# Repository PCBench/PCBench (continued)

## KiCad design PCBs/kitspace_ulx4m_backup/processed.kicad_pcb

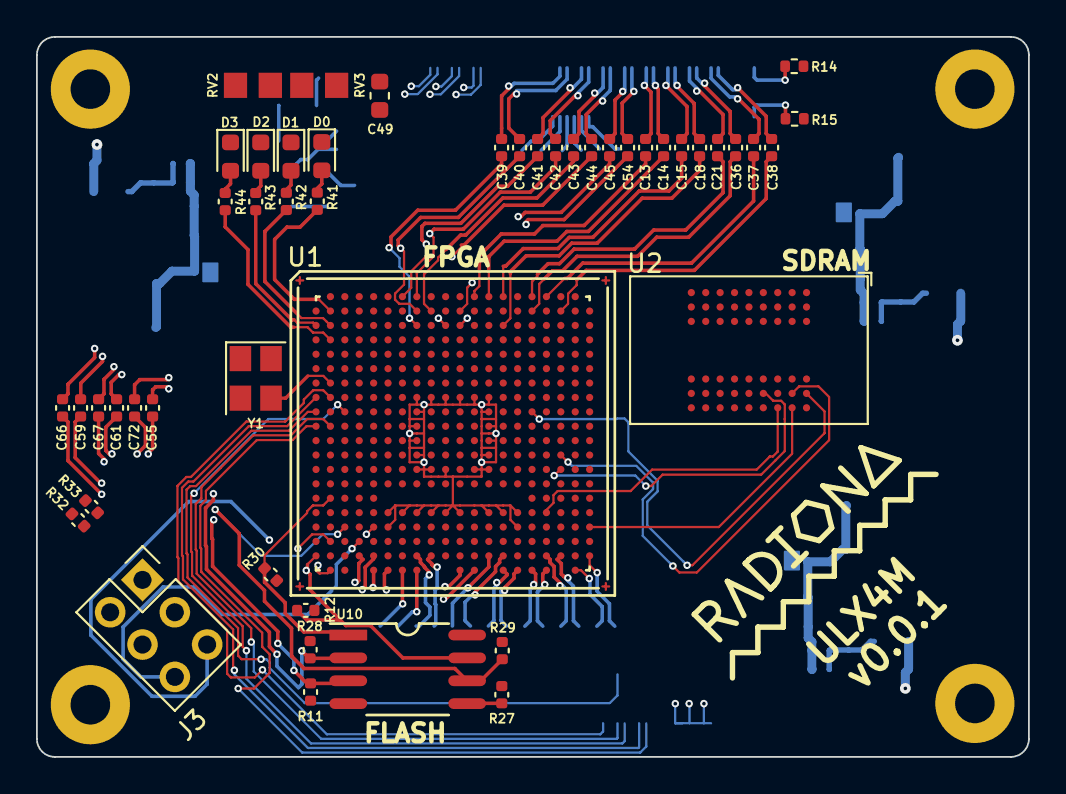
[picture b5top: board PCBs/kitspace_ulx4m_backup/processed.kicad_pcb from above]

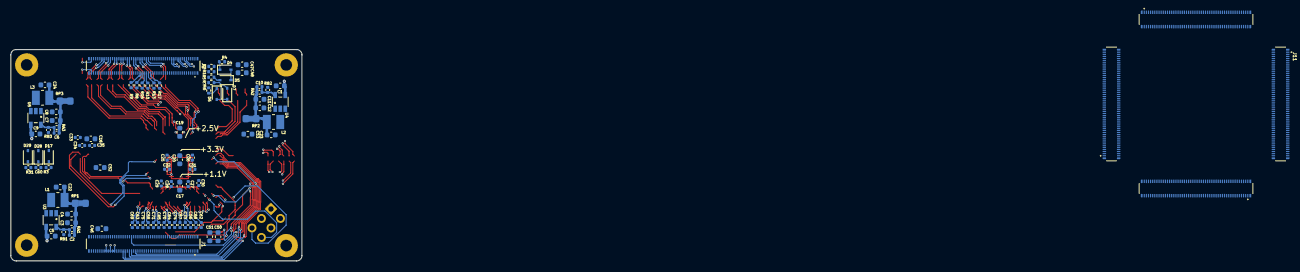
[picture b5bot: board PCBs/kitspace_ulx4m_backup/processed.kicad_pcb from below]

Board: 4 copper layers, 55.1 x 40.0 mm, 151 parts (96 on the bottom side), 108 nets.

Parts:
C1, C3, C4, C5, C7, C8, C9, C11, C12: 22uF; C_0603_1608Metric
C2, C6, C10: 100pF; C_0402_1005Metric
C13, C14, C15, C18, C21, C36, C37, C38, C39, C40, C41, C42, C43, C44, C45, C54: 100n; C_0402_1005Metric
C16, C17, C19, C20, C22, C23, C24, C46, C47: 2.2uF; C_0603_1608Metric
C25, C26, C27, C28, C29, C30, C31, C32, C33, C34, C35: 22nF; C_0402_1005Metric
C48, C49, C50, C51, C52, C53: 22nF; C_0603_1608Metric
C55, C56, C57, C58, C59, C61, C62, C63, C64, C65, C66, C67, C68, C69, C70, C71, C72, C73, C74, C75: 22n; C_0402_1005Metric
C60: 220nF; C_0402_1005Metric
D0: RED; LED_0603_1608Metric
D1: ORANGE; LED_0603_1608Metric
D2: GREEN; LED_0603_1608Metric
D3: BLUE; LED_0603_1608Metric
D4, D5, D6, D7, D17, D28, D29: 1N914; D_SOD-323
EMARD: emard12mm
EMARD#2: emard12mm
H1, H2, H3, H4: HOLE; MountingHole_3.2mm_M3_ISO14580_Pad
J1, J2, J9, J10, J11, J12: DF40C-100DP-0.4V(51); HRS_DF40C-100DP-0.4V(51)
J3: JTAG; PinSocket_2x03_P2.54mm_Vertical
L1, L2, L3: 2.2uH; L_1008_1210
R1, R2: 27; R_0402_1005Metric
R3, R30: 4.7k; C_0402_1005Metric
R4, R6: 1.1K; R_0402_1005Metric
R5, R7: 15K; R_0402_1005Metric
R8, R9, R16, R17: 100K; R_0402_1005Metric
R10, R13, R14, R15: 4K7; R_0402_1005Metric
R11, R12, R27, R28: 10k; C_0402_1005Metric
R29: 1.1k; C_0402_1005Metric
R31, R32, R33: 15k; C_0402_1005Metric
R41, R42, R43, R44: 549; C_0402_1005Metric
RA1, RA2, RA3: 15k; C_0402_1005Metric
RB1: 18k; C_0402_1005Metric
RB2: 4.7k; C_0402_1005Metric
RB3: 3.3k; C_0402_1005Metric
RP1, RP2, RP3: 0; R_0805_2012Metric_Pad1.29x1.40mm_HandSolder_Jumper_NC
RV2, RV3: 0; R_0805_2012Metric_Pad1.29x1.40mm_HandSolder
U1: LFE5U-85F-6BG381C; BGA-381_pitch0.8mm_dia0.4mm
U2: IS42S16320D-6BLI
U3, U4, U5: TLV62569DBV; TSOT-25
U10: IS25LP128F-JBLE; SOA008-150-208mil
Y1: FNETHE025; Crystal_SMD_TXC_7M-4Pin_3.2x2.5mm
fer: fer; fer4mm6
koncar: koncar
radiona: radiona

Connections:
+1V1: U1.H8, U1.H9, U1.H10, U1.H11, U1.H12, U1.H13, U1.J8, U1.J13, U1.K8, U1.K13, U1.L8, U1.L13, U1.M8, U1.M13, U1.N8, U1.N9, U1.N10, U1.N12, U1.N13, U1.T6, U1.T7, U1.T8, U1.T9, U1.T10, U1.T11, U1.T13, U1.T14, U1.T15, U1.U6, U1.U15
+5V: C1.1, C5.1, C9.1, J1.77, J1.79, J1.81, J1.85, J1.87, U3.4, U4.4, U5.4
/blinkey/ALED0: D0.2, R41.2
/blinkey/ALED1: D1.2, R42.2
/blinkey/ALED2: D2.2, R43.2
/blinkey/ALED3: D3.2, R44.2
/flash/FLASH_MISO: R28.2, U1.V2, U10.2
/flash/FLASH_MOSI: R27.2, U10.5
/flash/FLASH_SCK: R29.2, U1.U3, U10.6
/flash/FLASH_nCS: R30.2, U1.R2, U10.1
/flash/FLASH_nHOLD: R12.2, U1.W1, U10.7
/flash/FLASH_nWP: R11.2, U1.Y2, U10.3
/power/FB1: C2.2, RA1.2, RB1.2, U3.5
/power/FB2: C10.2, RA2.2, RB2.2, U4.5
/power/FB3: C6.2, RA3.2, RB3.2, U5.5
/power/P1V1: C2.1, C3.1, C4.1, C22.1, L1.2, RA1.1
/power/P2V5: C10.1, C11.1, C12.1, C23.1, L2.2, RA2.1
/power/P3V3: C6.1, C7.1, C8.1, C24.1, L3.2, RA3.1
/serdes/CLK_0_N: C66.1, U1.Y12
/serdes/CLK_0_P: C59.2, U1.Y11
/serdes/CLK_1_N: C69.1, U1.W20
/serdes/CLK_1_P: C63.2, U1.Y19
/serdes/S_0_N: C67.1, U1.Y6
/serdes/S_0_P: C61.2, U1.Y5
/serdes/S_1_N: C68.1, U1.Y8
/serdes/S_1_P: C62.2, U1.Y7
/serdes/S_2_N: C72.1, U1.W5
/serdes/S_2_P: C55.2, U1.W4
/serdes/S_3_N: C73.1, U1.W9
/serdes/S_3_P: C56.2, U1.W8
/serdes/S_4_N: C70.1, U1.Y15
/serdes/S_4_P: C64.2, U1.Y14
/serdes/S_5_N: C71.1, U1.Y17
/serdes/S_5_P: C65.2, U1.Y16
/serdes/S_6_N: C74.1, U1.W14
/serdes/S_6_P: C57.2, U1.W13
/serdes/S_7_N: C75.1, U1.W18
/serdes/S_7_P: C58.2, U1.W17
CLK_25MHz: U1.G2, Y1.3
FPDI_CLK+: C37.1, U1.A17
FPDI_CLK-: C38.1, U1.B18
FPDI_D0+: C21.1, U1.A16
FPDI_D0-: C36.1, U1.B16
FPDI_D1+: C15.1, U1.A14
FPDI_D1-: C18.1, U1.C14
FPDI_D2+: C13.1, U1.A12
FPDI_D2-: C14.1, U1.A13
GN0: C54.1, U1.C11
GN3: C44.1, U1.C10
GN4: C42.1, U1.A8
GN5: C40.1, U1.B8
GP0: C45.1, U1.B11
GP3: C43.1, U1.B9
GP4: C41.1, U1.A7
GP5: C39.1, U1.C8
HDMI0_CEC: J2.51, R8.2
HDMI0_CLK_N: C38.2, J2.90
HDMI0_CLK_P: C37.2, J2.88
HDMI0_HOTPLUG: J2.53, R9.2
HDMI0_SCL: J2.100, R14.2
HDMI0_SDA: J2.99, R15.2
HDMI0_TX0_N: C36.2, J2.84
HDMI0_TX0_P: C21.2, J2.82
HDMI0_TX1_N: C18.2, J2.78
HDMI0_TX1_P: C15.2, J2.76
HDMI0_TX2_N: C14.2, J2.72
HDMI0_TX2_P: C13.2, J2.70
HDMI1_CEC: J2.49, R16.2
HDMI1_CLK_N: C54.2, J2.66
HDMI1_CLK_P: C45.2, J2.64
HDMI1_HOTPLUG: J2.43, R17.2
HDMI1_SCL: J2.47, R10.2
HDMI1_SDA: J2.45, R13.2
HDMI1_TX0_N: C44.2, J2.60
HDMI1_TX0_P: C43.2, J2.58
HDMI1_TX1_N: C42.2, J2.54
HDMI1_TX1_P: C41.2, J2.52
HDMI1_TX2_N: C40.2, J2.48
HDMI1_TX2_P: C39.2, J2.46
JTAG_TDO: J3.6, U1.V4
JTAG_TMS: J3.5, U1.U5
LED0: R41.1, U1.B2
LED1: R42.1, U1.C2
LED2: R43.1, U1.C1
LED3: R44.1, U1.D2
unnamed: D4.1, R4.1
unnamed: D5.2, R5.1
unnamed: D6.1, R6.1
unnamed: D7.2, R7.1
PCIe_CLK_N: C66.2, J2.12
PCIe_CLK_P: C59.1, J2.10
PCIe_RX_N: C67.2, J2.18
PCIe_RX_P: C61.1, J2.16
PCIe_TX_N: C72.2, J2.24
PCIe_TX_P: C55.1, J2.22
SDRAM_D0: U1.J16, U2.A8
SDRAM_D2: U1.M18, U2.B8
SDRAM_D3: U1.N18, U2.D8
SDRAM_D6: U1.T17, U2.C9
SDRAM_D7: U1.U20, U2.B9
SD_CLK: J1.57, U1.H2
SD_CMD: J1.62, U1.J1
SD_D0: J1.63, U1.J3
SD_D1: J1.67, U1.H1
SD_D2: J1.69, U1.K1
SD_D3: J1.61, U1.K2
USB_FPGA_PULL_D+: D4.2, D5.1
USB_FPGA_PULL_D-: D6.2, D7.1

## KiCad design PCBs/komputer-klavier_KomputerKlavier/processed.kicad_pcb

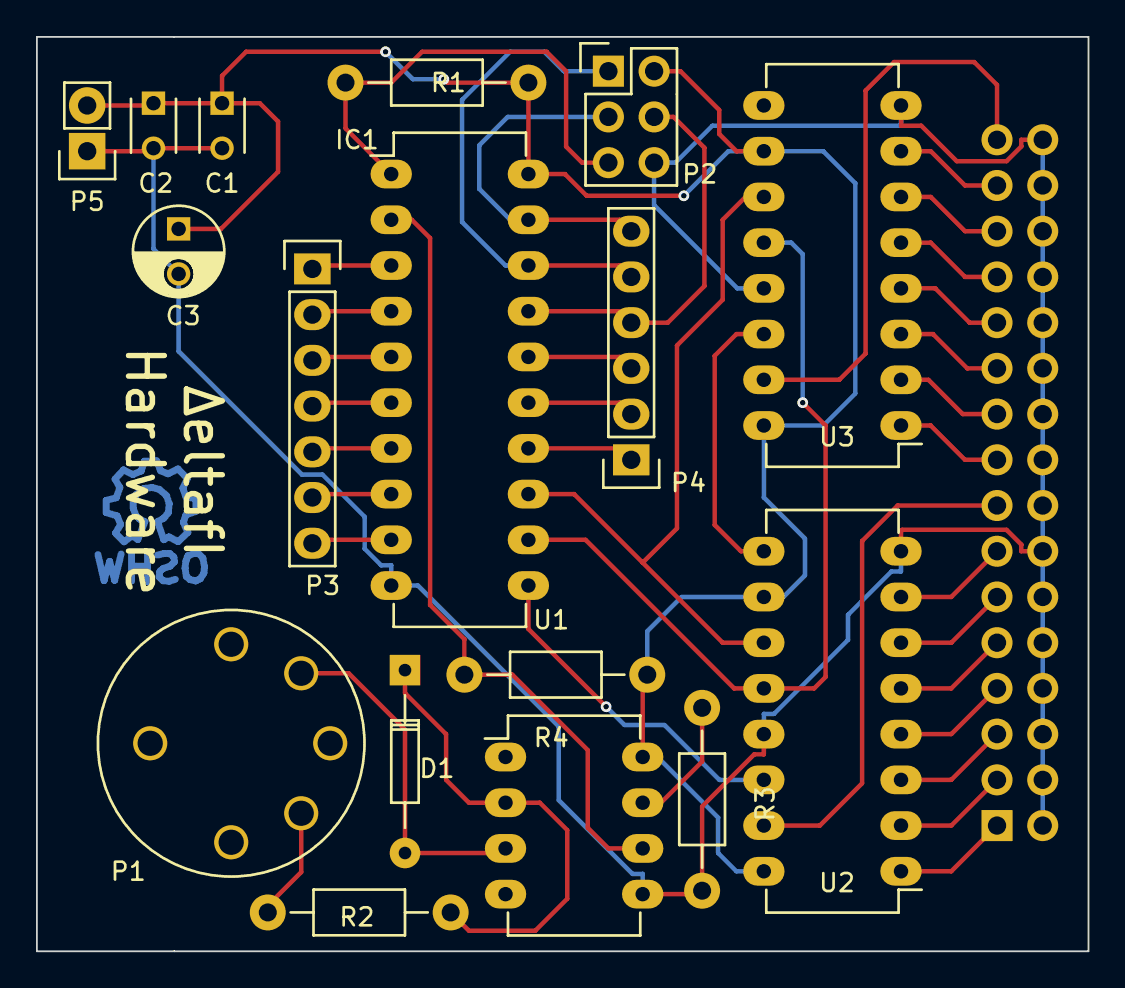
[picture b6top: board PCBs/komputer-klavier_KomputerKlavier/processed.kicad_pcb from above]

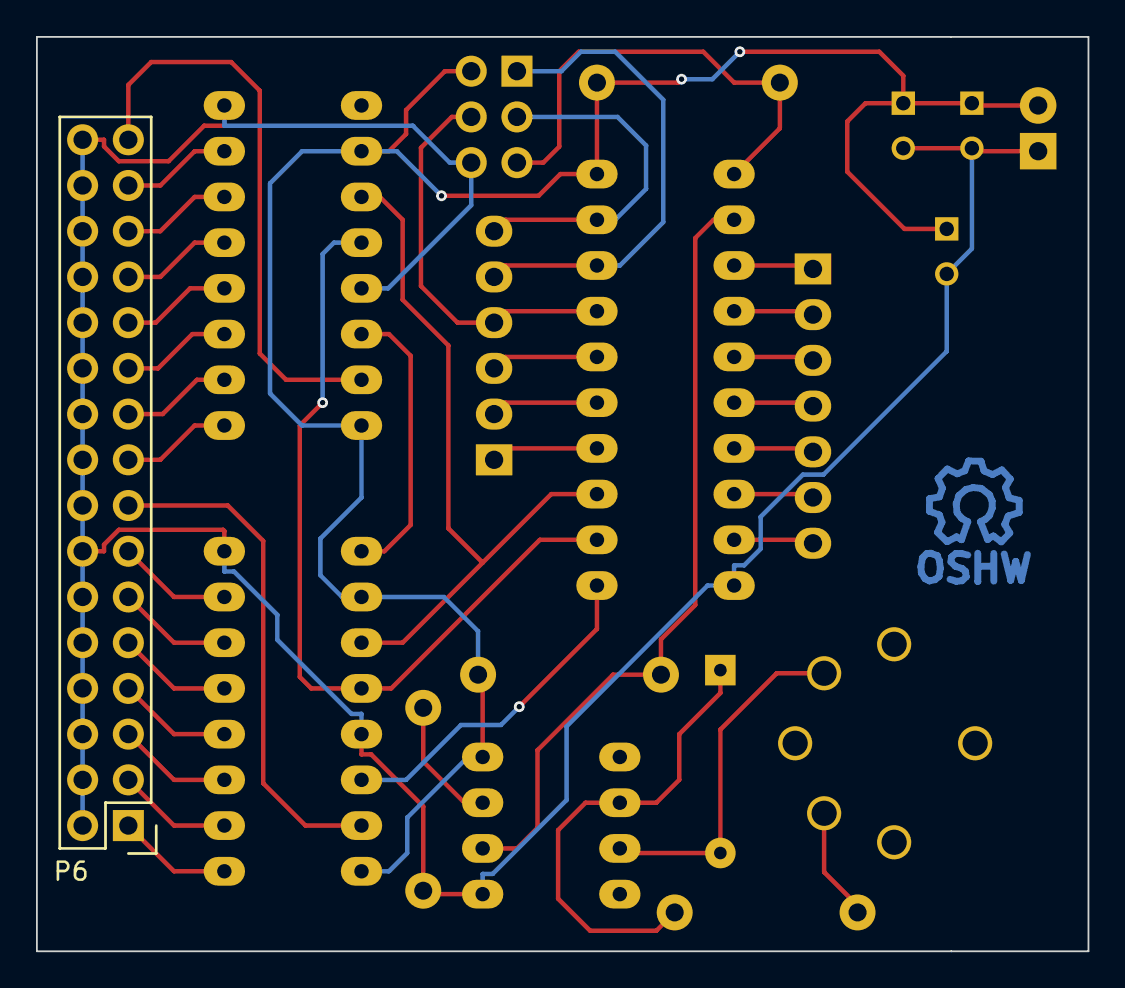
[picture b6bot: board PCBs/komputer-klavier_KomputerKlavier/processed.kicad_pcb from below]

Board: 2 copper layers, 58.4 x 50.8 mm, 19 parts (2 on the bottom side), 41 nets.

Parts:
C1, C2: 100nf; C_Disc_D3_P2.5
C3: 1uf; C_Radial_D5_L6_P2.5
D1: 1N4148; Diode_DO-35_SOD27_Horizontal_RM10
IC1: ATTINY4313-P; DIP-20_W7.62mm_LongPads
Noname_1: Symbol_OSHW-Logo_CopperTop
P1: DIN_5
P2: CONN_02X03; Pin_Header_Straight_2x03
P3: CONN_01X07; Pin_Header_Straight_1x07
P4: CONN_01X06; Pin_Header_Straight_1x06
P5: CONN_01X02; Pin_Header_Straight_1x02
P6: CONN_02X16; Pin_Header_Straight_2x16
R1: 10k; Resistor_Horizontal_RM10mm
R2: 220; Resistor_Horizontal_RM10mm
R3: 1k; Resistor_Horizontal_RM10mm
R4: 470; Resistor_Horizontal_RM10mm
U1: 6N136; DIP-8_W7.62mm_LongPads
U2, U3: 74HC595; DIP-16_W7.62mm_LongPads

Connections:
GND: C1.2, C2.2, C3.2, IC1.10, P2.6, P5.1, P6.2, P6.4, P6.6, P6.8, P6.10, P6.12, P6.14, P6.16, P6.18, P6.20, P6.22, P6.24, P6.26, P6.28, P6.30, P6.32, R3.2, U1.5, U2.8, U2.13, U3.8, U3.13
unnamed: D1.1, R2.1, U1.2
unnamed: D1.2, P1.5, U1.3
unnamed: IC1.1, P2.5, R1.2
unnamed: IC1.2, R4.2, U1.6
unnamed: IC1.3, P3.1
unnamed: IC1.4, P3.2
unnamed: IC1.5, P3.3
unnamed: IC1.6, P3.4
unnamed: IC1.7, P3.5
unnamed: IC1.8, P3.6
unnamed: IC1.9, P3.7
unnamed: IC1.11, U2.14
unnamed: IC1.12, U2.12, U3.12
unnamed: IC1.13, U2.11, U3.11
unnamed: IC1.14, P4.1
unnamed: IC1.15, P4.2
unnamed: IC1.16, P4.3
unnamed: IC1.17, P2.4, P4.4
unnamed: IC1.18, P2.1, P4.5
unnamed: IC1.19, P2.3, P4.6
unnamed: P1.4, R2.2
unnamed: P6.1, U2.1
unnamed: P6.3, U2.2
unnamed: P6.5, U2.3
unnamed: P6.7, U2.4
unnamed: P6.9, U2.5
unnamed: P6.11, U2.6
unnamed: P6.13, U2.7
unnamed: P6.15, U2.15
unnamed: P6.17, U3.1
unnamed: P6.19, U3.2
unnamed: P6.21, U3.3
unnamed: P6.23, U3.4
unnamed: P6.25, U3.5
unnamed: P6.27, U3.6
unnamed: P6.29, U3.7
unnamed: P6.31, U3.15
unnamed: R3.1, U1.7
unnamed: U2.9, U3.14
VCC: C1.1, C2.1, C3.1, IC1.20, P2.2, P5.2, R1.1, R4.1, U1.8, U2.10, U2.16, U3.10, U3.16

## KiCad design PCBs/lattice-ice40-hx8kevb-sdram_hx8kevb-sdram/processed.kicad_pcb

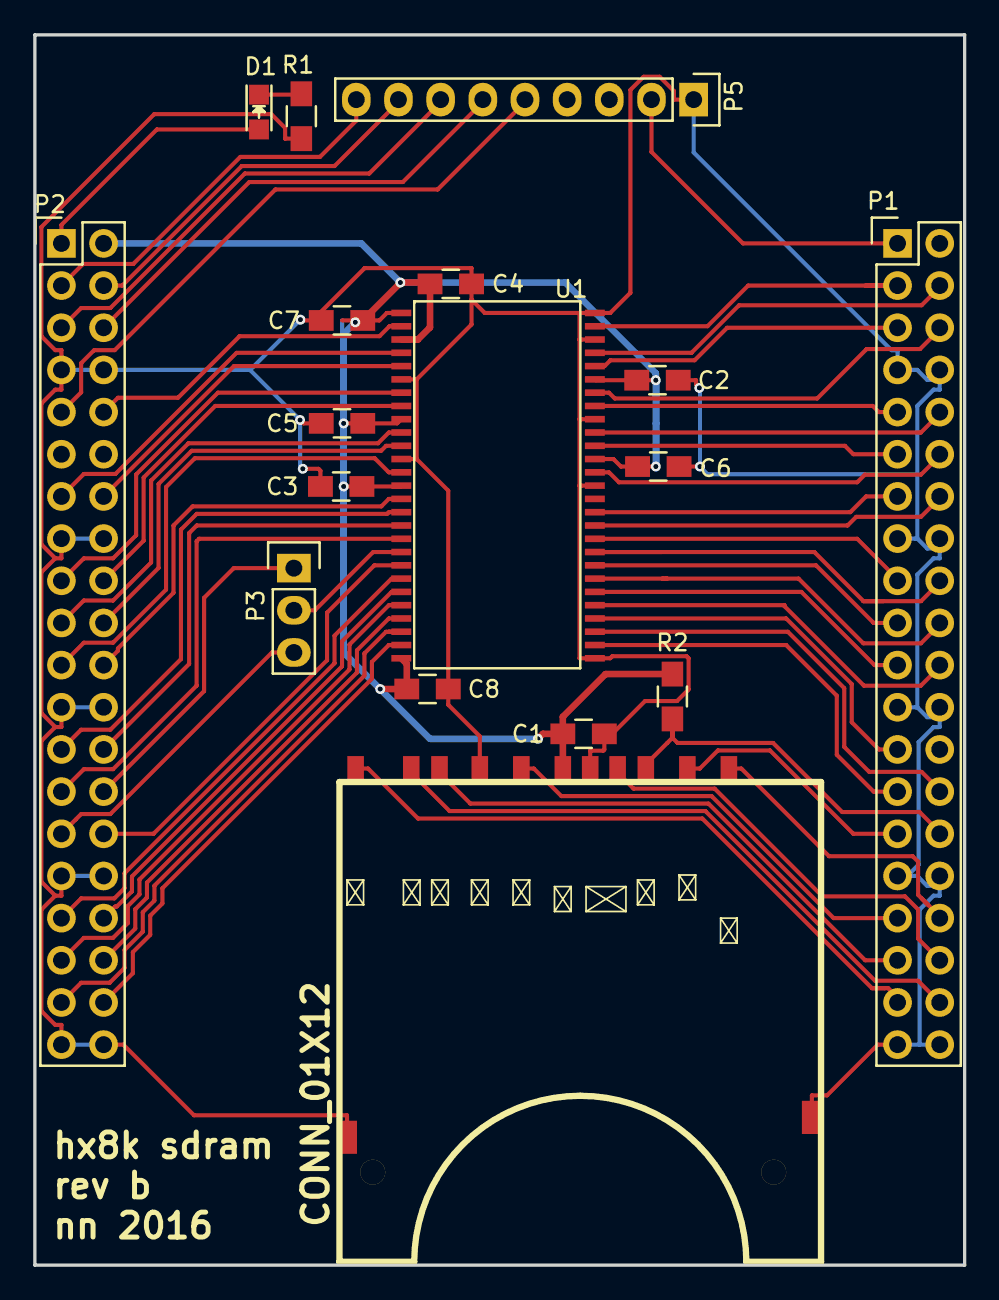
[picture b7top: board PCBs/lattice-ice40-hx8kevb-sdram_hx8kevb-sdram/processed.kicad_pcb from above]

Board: 2 copper layers, 56.0 x 74.1 mm, 17 parts (0 on the bottom side), 59 nets.

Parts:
C1, C2, C3, C4, C5, C6, C7, C8: C; C_0805_HandSoldering
D1: LED; LED_0805
P1, P2: CONN_02X20; Pin_Header_Straight_2x20
P3: CONN_01X03; Pin_Header_Straight_1x03
P4: CONN_01X12; SD_CARD_10100
P5: CONN_01X09; Pin_Header_Straight_1x09
R1, R2: R; R_0805_HandSoldering
U1: AS4C16M16; TSOP-54

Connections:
+3V3: C1.1, C2.1, C3.1, C4.1, C5.2, C6.2, C7.2, C8.1, P2.2, P4.4, R2.1, U1.1, U1.3, U1.9, U1.14, U1.27, U1.43, U1.49
/A0: P2.35, U1.23
/A1: P2.36, U1.24
/A2: P2.37, U1.25
/A3: P2.38, U1.26
/A4: P1.27, U1.29
/A5: P1.28, U1.30
/A6: P1.25, U1.31
/A7: P1.22, U1.32
/A8: P1.21, U1.33
/A9: P1.20, U1.34
/A10: P2.34, U1.22
/A11: P1.19, U1.35
/A12: P1.18, U1.36
/BA0: P2.30, U1.20
/BA1: P2.33, U1.21
/CAS: P2.26, U1.17
/CKE: P1.17, U1.37
/CLK: P1.14, U1.38
/CS: P3.2, U1.19
/CS1: P2.28, P3.1
/CS2: P2.29, P3.3
/DQ0: P2.10, U1.2
/DQ1: P2.13, U1.4
/DQ2: P2.14, U1.5
/DQ3: P2.17, U1.7
/DQ4: P2.18, U1.8
/DQ5: P2.19, U1.10
/DQ6: P2.20, U1.11
/DQ7: P2.21, U1.13
/DQ8: P1.12, U1.42
/DQ9: P1.11, U1.44
/DQ10: P1.10, U1.45
/DQ11: P1.9, U1.47
/DQ12: P1.6, U1.48
/DQ13: P1.5, U1.50
/DQ14: P1.4, U1.51
/DQ15: P1.3, U1.53
/GPIO1: P2.3, P5.9
/GPIO2: P2.4, P5.8
/GPIO3: P2.5, P5.7
/GPIO4: P2.6, P5.6
/GPIO5: P2.9, P5.5
/GPIO8: P1.1, P5.2
/LDQM: P2.22, U1.15
/LED: D1.2, P2.1
/RAS: P2.27, U1.18
/SD_CD: P1.36, P4.10
/SD_CLK: P1.33, P4.5
/SD_CMD: P1.30, P4.2, R2.2
/SD_D0: P1.35, P4.7
/SD_D1: P1.38, P4.8
/SD_D2: P1.34, P4.9
/SD_D3: P1.29, P4.1
/SD_WP: P1.37, P4.11
/UDQM: P1.13, U1.39
/WE: P2.25, U1.16
GND: C1.2, C2.2, C3.2, C4.2, C5.1, C6.1, C7.1, C8.2, P1.7, P1.8, P1.15, P1.16, P1.23, P1.24, P1.31, P1.32, P1.39, P1.40, P2.7, P2.8, P2.15, P2.16, P2.23, P2.24, P2.31, P2.32, P2.39, P2.40, P4.3, P4.6, P4.12, P5.1, R1.2, U1.6, U1.12, U1.28, U1.41, U1.46, U1.52, U1.54
unnamed: D1.1, R1.1

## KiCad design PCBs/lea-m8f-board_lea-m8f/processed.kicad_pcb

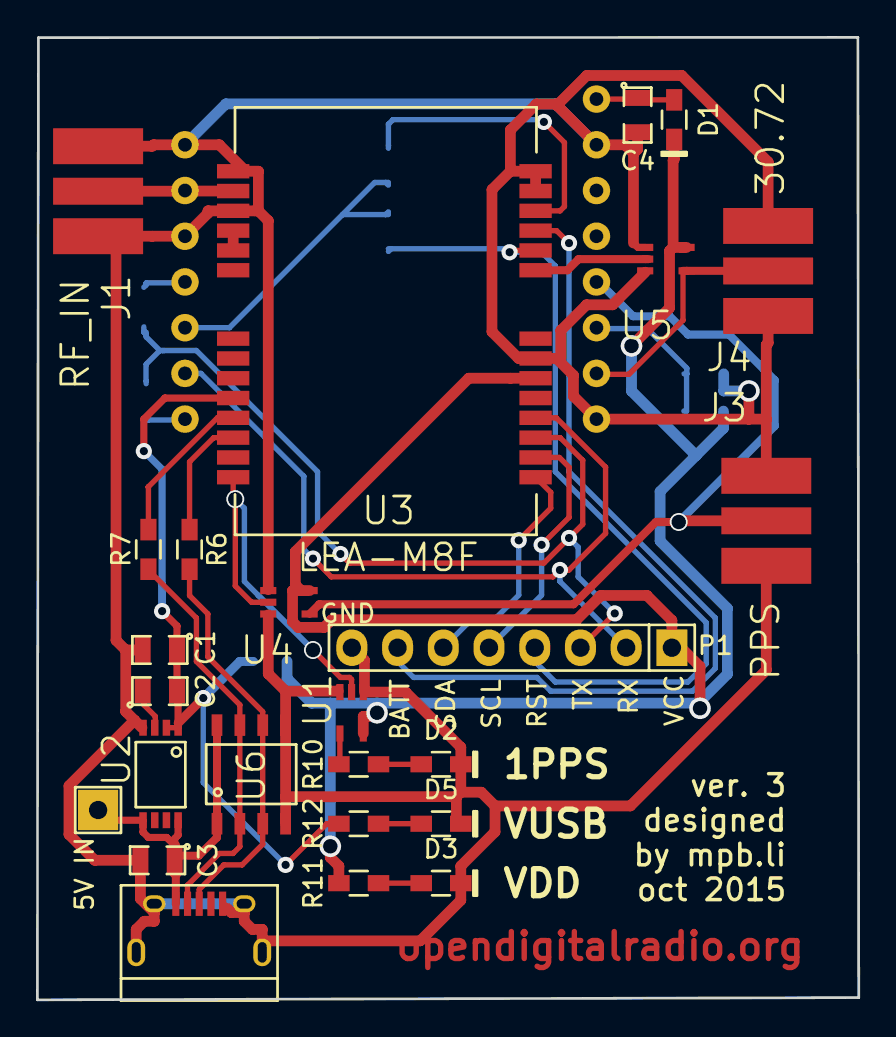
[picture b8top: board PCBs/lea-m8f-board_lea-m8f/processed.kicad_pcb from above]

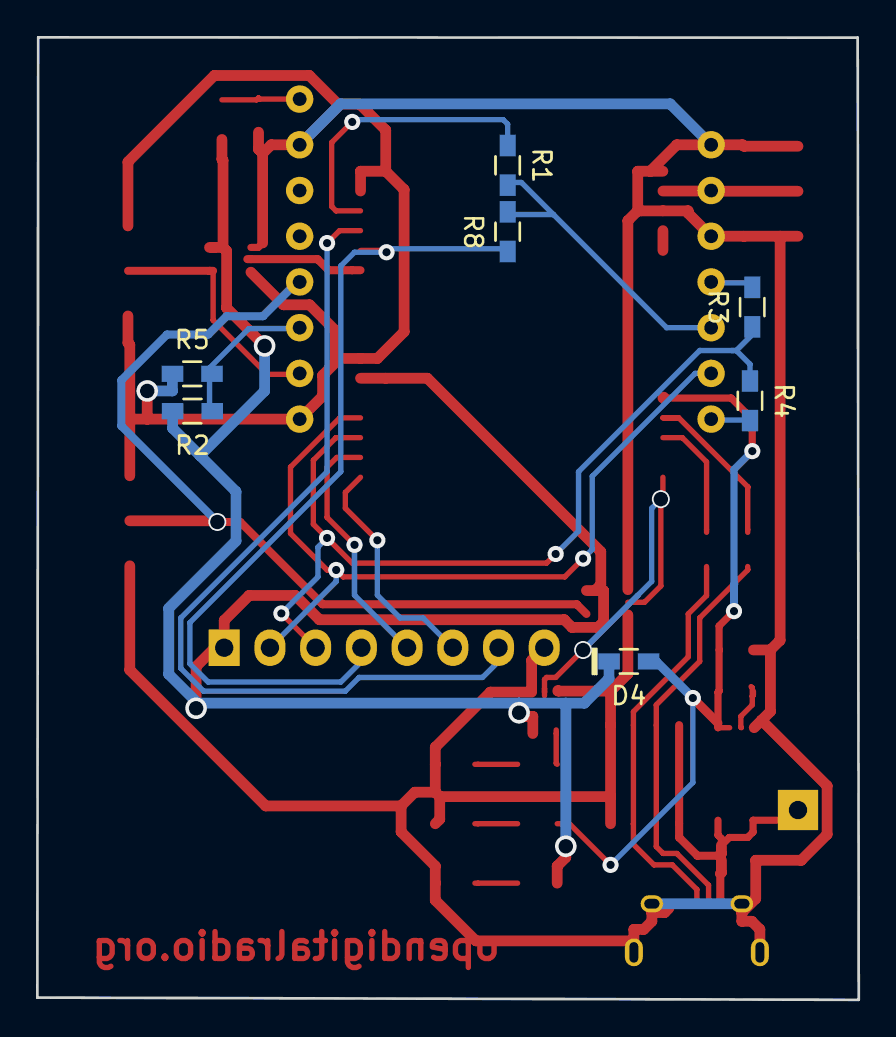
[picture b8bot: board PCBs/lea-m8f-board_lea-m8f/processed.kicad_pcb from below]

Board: 2 copper layers, 45.6 x 53.5 mm, 33 parts (7 on the bottom side), 31 nets.

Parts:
C1: 10uF; SMD-0805
C2: 10nF; SMD-0805
C3, C4: 1uF; SMD-0805
CON1: USB-MICRO-B; USB_Micro-B
D1, D4: DIODESCH; Diode_0603_HandSoldering
D2: PPS; Diode_0603_HandSoldering
D3: VDD; Diode_0603_HandSoldering
D5: VUSB; Diode_0603_HandSoldering
J1: RF_IN; SMA_SIDE
J3: PPS; SMA_SIDE
J4: 30.72; SMA_SIDE
P1: CONN_01X08; Pin_Header_Straight_1x08
P2: 5V IN; Pin_Header_Straight_1x01
R1, R5, R8: DNF; R_0603_HandSoldering
R2, R3, R4: 0; R_0603_HandSoldering
R6, R7: 27; R_0603_HandSoldering
R10, R11, R12: 510; R_0603_HandSoldering
U1, U4, U5: NC7SZ125; SC70
U2: LT1962; MS8
U3: LEA-M8F; LEA
U6: USB6B1; SO-8
U100: B200_GPSDO; GPSDO_B200

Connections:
/5VUSB: C3.1, CON1.1, P2.1, U2.5, U2.8, U6.1, U6.8
/ISP_N: R1.2, R8.2, U100.13
/LOCK: R2.1, R5.2, U100.3
/M8F_PPS: U1.2, U3.28, U4.2
/PPS_BUFF: J3.2, U4.4, U100.4
/REFCLK: U3.9, U5.2
/REFCLK_BUFF: J4.2, U5.4, U100.2
/RESET_N: P1.4, R8.1, U3.10
/RF_IN: J1.2, U3.16, U100.10
/RXD: P1.2, U3.4, U100.14
/SB_N: R1.1, U3.12
/SCL: P1.5, U3.2
/SDA: P1.6, U3.1
/TXD: P1.3, R3.1, R4.1, U3.3
/VANT: U3.18, U3.19
/VBKP: P1.7, U3.11
/VDDUSB: C1.1, C2.2, D4.1, R12.1, U2.1, U2.2, U3.24
/VDD_B200: C4.1, D1.1, U100.8
GND: C1.2, C3.2, C4.2, CON1.5, CON1.6, CON1.7, CON1.8, CON1.9, D2.2, D3.2, D5.2, J1.1, J1.3, J3.1, J3.3, J4.1, J4.3, P1.8, R5.1, U1.1, U1.3, U2.4, U3.7, U3.13, U3.14, U3.15, U3.17, U4.1, U4.3, U5.1, U5.3, U6.4, U6.5, U100.1, U100.7, U100.9, U100.11
unnamed: C2.1, U2.3
unnamed: CON1.2, R7.1, U6.2, U6.7
unnamed: CON1.3, R6.1, U6.3, U6.6
unnamed: D2.1, R10.2
unnamed: D3.1, R11.1
unnamed: D5.1, R12.2
unnamed: R3.2, U100.12
unnamed: R4.2, U100.15
unnamed: R6.2, U3.26
unnamed: R7.2, U3.25
unnamed: R10.1, U1.4
VCC: D1.2, D4.2, P1.1, R2.2, R11.2, U1.5, U3.6, U4.5, U5.5
